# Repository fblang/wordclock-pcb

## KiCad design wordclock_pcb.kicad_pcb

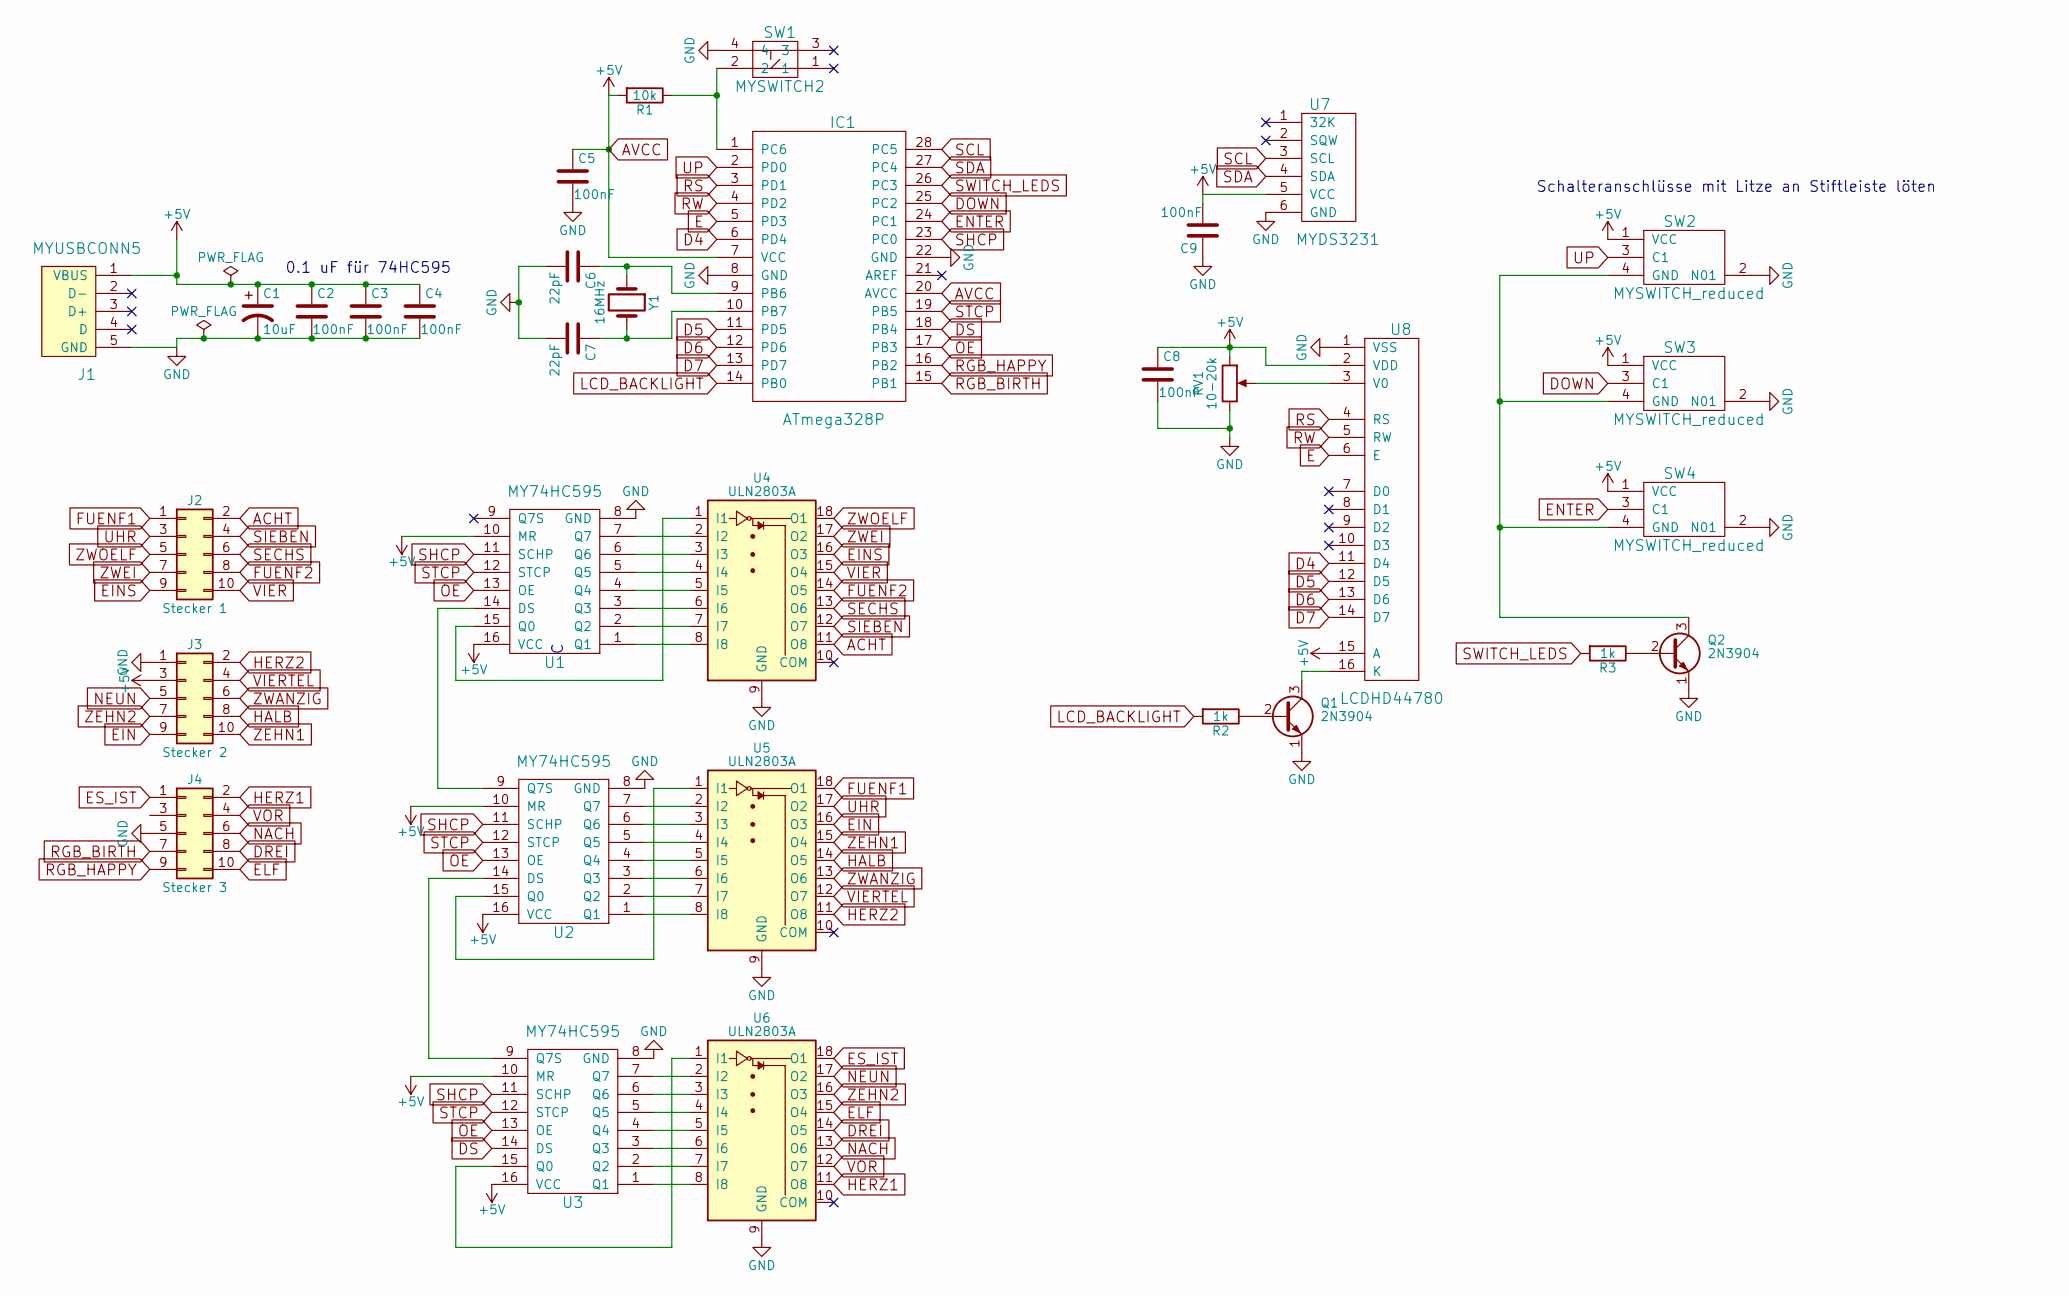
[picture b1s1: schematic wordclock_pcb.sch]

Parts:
C1: 10uF; C_Disc_D4.3mm_W1.9mm_P5.00mm
C2, C3, C4, C5, C8, C9: 100nF; C_Disc_D4.3mm_W1.9mm_P5.00mm
C6, C7: 22pF; C_Disc_D4.3mm_W1.9mm_P5.00mm
IC1: ATmega328P; DIP-28_W7.62mm_Socket_LongPads
J1: MYUSBCONN5; Pin_Header_Straight_1x05_Pitch2.54mm
J2: Stecker 1; Pin_Header_Straight_2x05_Pitch2.54mm
J3: Stecker 2; Pin_Header_Straight_2x05_Pitch2.54mm
J4: Stecker 3; Pin_Header_Straight_2x05_Pitch2.54mm
Q1, Q2: 2N3904; TO-92_Inline_Wide
R1: 10k; R_Axial_DIN0207_L6.3mm_D2.5mm_P10.16mm_Horizontal
R2, R3: 1k; R_Axial_DIN0207_L6.3mm_D2.5mm_P10.16mm_Horizontal
RV1: 10-20k; Potentiometer_Trimmer_ACP_CA9v_Horizontal_Px10.0mm_Py5.0mm
SW1: MYSWITCH2; SW_TH_Tactile_Omron_B3F-10xx
SW2: MYSWITCH_reduced
SW3, SW4: MYSWITCH_reduced; Pin_Header_Straight_1x04_Pitch2.54mm
U1, U2, U3: MY74HC595; DIP-16_W7.62mm_LongPads
U4, U5, U6: ULN2803A; DIP-18_W7.62mm_Socket_LongPads
U7: MYDS3231; Pin_Header_Straight_1x06_Pitch2.54mm
U8: LCDHD44780; Pin_Header_Straight_1x16_Pitch2.54mm
Y1: 16MHz; Crystal_HC49-4H_Vertical

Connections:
ACHT: J2.2, U4.11 (O8)
AVCC: C1.1, C2.1, C3.1, C4.1, C5.1, C8.1, C9.2, IC1.7 (VCC), IC1.20 (AVCC), J1.1 (VBUS), J3.3, R1.2, RV1.1, SW2.1 (VCC), SW3.1 (VCC), SW4.1 (VCC), U1.10 (MR), U1.16 (VCC), U2.10 (MR), U2.16 (VCC), U3.10 (MR), U3.16 (VCC), U7.5 (VCC), U8.2 (VDD), U8.15 (A)
D4: IC1.6 (PD4), U8.11 (D4)
D5: IC1.11 (PD5), U8.12 (D5)
D6: IC1.12 (PD6), U8.13 (D6)
D7: IC1.13 (PD7), U8.14 (D7)
DOWN: IC1.25 (PC2), SW3.3 (C1)
DREI: J4.8, U6.14 (O5)
DS: IC1.18 (PB4), U3.14 (DS)
E: IC1.5 (PD3), U8.6 (E)
EIN: J3.9, U5.16 (O3)
EINS: J2.9, U4.16 (O3)
ELF: J4.10, U6.15 (O4)
ENTER: IC1.24 (PC1), SW4.3 (C1)
ES_IST: J4.1, U6.18 (O1)
FUENF1: J2.1, U5.18 (O1)
FUENF2: J2.8, U4.14 (O5)
GND: C1.2, C2.2, C3.2, C4.2, C5.2, C6.2, C7.2, C8.2, C9.1, IC1.8 (GND), IC1.22 (GND), J1.5 (GND), J3.1, J4.5, Q1.1 (E), Q2.1 (E), RV1.3, SW1.4, SW2.2 (N01), SW3.2 (N01), SW4.2 (N01), U1.8 (GND), U2.8 (GND), U3.8 (GND), U4.9 (GND), U5.9 (GND), U6.9 (GND), U7.6 (GND), U8.1 (VSS)
HALB: J3.8, U5.14 (O5)
HERZ1: J4.2, U6.11 (O8)
HERZ2: J3.2, U5.11 (O8)
LCD_BACKLIGHT: IC1.14 (PB0), R2.2
NACH: J4.6, U6.13 (O6)
NEUN: J3.5, U6.17 (O2)
unnamed: C6.1, IC1.9 (PB6), Y1.1
unnamed: C7.1, IC1.10 (PB7), Y1.2
unnamed: IC1.1 (PC6), R1.1, SW1.2
unnamed: Q1.2 (B), R2.1
unnamed: Q1.3 (C), U8.16 (K)
unnamed: Q2.2 (B), R3.1
unnamed: Q2.3 (C), SW2.4 (GND), SW3.4 (GND), SW4.4 (GND)
unnamed: RV1.2, U8.3 (V0)
unnamed: U1.1 (Q1), U4.8 (I8)
unnamed: U1.2 (Q2), U4.7 (I7)
unnamed: U1.3 (Q3), U4.6 (I6)
unnamed: U1.4 (Q4), U4.5 (I5)
unnamed: U1.5 (Q5), U4.4 (I4)
unnamed: U1.6 (Q6), U4.3 (I3)
unnamed: U1.7 (Q7), U4.2 (I2)
unnamed: U1.14 (DS), U2.9 (Q7S)
unnamed: U1.15 (Q0), U4.1 (I1)
unnamed: U2.1 (Q1), U5.8 (I8)
unnamed: U2.2 (Q2), U5.7 (I7)
unnamed: U2.3 (Q3), U5.6 (I6)
unnamed: U2.4 (Q4), U5.5 (I5)
unnamed: U2.5 (Q5), U5.4 (I4)
unnamed: U2.6 (Q6), U5.3 (I3)
unnamed: U2.7 (Q7), U5.2 (I2)
unnamed: U2.14 (DS), U3.9 (Q7S)
unnamed: U2.15 (Q0), U5.1 (I1)
unnamed: U3.1 (Q1), U6.8 (I8)
unnamed: U3.2 (Q2), U6.7 (I7)
unnamed: U3.3 (Q3), U6.6 (I6)
unnamed: U3.4 (Q4), U6.5 (I5)
unnamed: U3.5 (Q5), U6.4 (I4)
unnamed: U3.6 (Q6), U6.3 (I3)
unnamed: U3.7 (Q7), U6.2 (I2)
unnamed: U3.15 (Q0), U6.1 (I1)
OE: IC1.17 (PB3), U1.13 (OE), U2.13 (OE), U3.13 (OE)
RGB_BIRTH: IC1.15 (PB1), J4.7
RGB_HAPPY: IC1.16 (PB2), J4.9
RS: IC1.3 (PD1), U8.4 (RS)
RW: IC1.4 (PD2), U8.5 (RW)
SCL: IC1.28 (PC5), U7.3 (SCL)
SDA: IC1.27 (PC4), U7.4 (SDA)
SECHS: J2.6, U4.13 (O6)
SHCP: IC1.23 (PC0), U1.11 (SCHP), U2.11 (SCHP), U3.11 (SCHP)
SIEBEN: J2.4, U4.12 (O7)
STCP: IC1.19 (PB5), U1.12 (STCP), U2.12 (STCP), U3.12 (STCP)
SWITCH_LEDS: IC1.26 (PC3), R3.2
UHR: J2.3, U5.17 (O2)
UP: IC1.2 (PD0), SW2.3 (C1)
VIER: J2.10, U4.15 (O4)
VIERTEL: J3.4, U5.12 (O7)
VOR: J4.4, U6.12 (O7)
ZEHN1: J3.10, U5.15 (O4)
ZEHN2: J3.7, U6.16 (O3)
ZWANZIG: J3.6, U5.13 (O6)
ZWEI: J2.7, U4.17 (O2)
ZWOELF: J2.5, U4.18 (O1)

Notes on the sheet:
Schalteranschlüsse mit Litze an Stiftleiste löten
0.1 uF für 74HC595

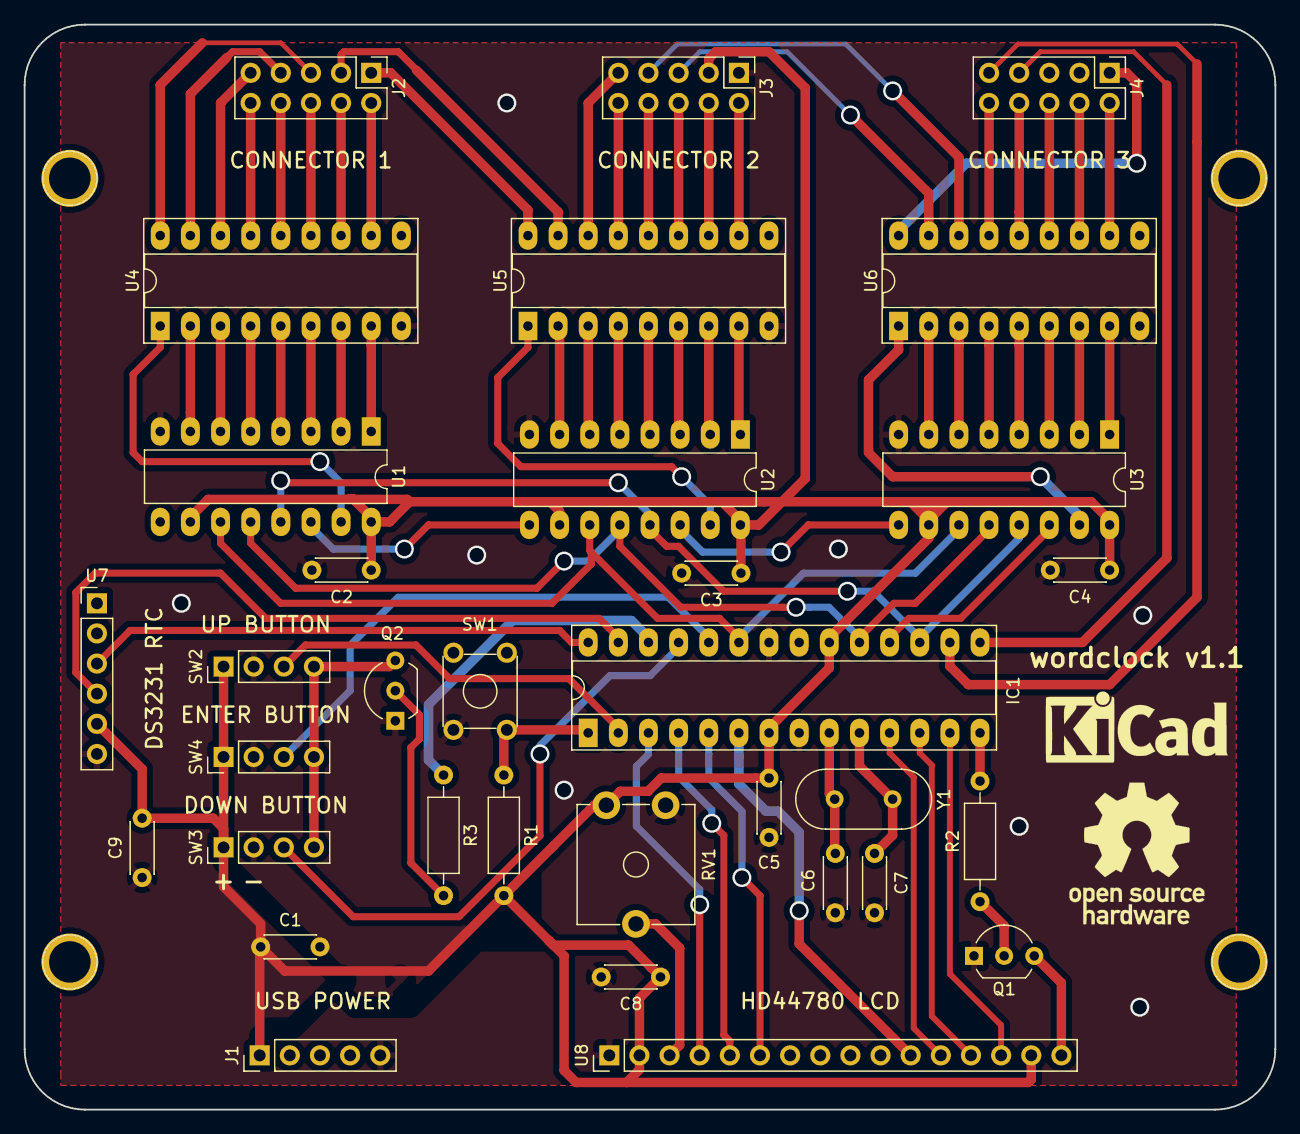
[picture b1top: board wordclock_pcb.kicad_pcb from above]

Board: 2 copper layers, 105.4 x 91.4 mm, 33 parts (0 on the bottom side), 80 nets.

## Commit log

2019-11-08 Initial commit. Revision 1
2019-11-10 First two layer version, needs refinement
2019-11-11 Change button order, tidy up some traces
2019-11-13 Add labeling to silkscreen, fix incorrect courtyard of SW1
2019-11-14 Add description
2019-11-17 Widen traces and add logos
2019-12-02 Enlarge text on silkscreen, fix positioning, addpolarity symbols for buttons
